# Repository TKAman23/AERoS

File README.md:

# AERoS
## An All-Encompassing Rocket System

A high-performance, compact rocket flight controller board designed around the **STM32F411RET6** microcontroller. This board integrates power management, sensor telemetry, state logging, and servo control into a single-cell Li-Po powered solution optimized for model rocketry and high-altitude aerospace tracking.

## **CRITICAL DISCLAIMER:**
*This board is currently in the active development phase. It has been fully routed and designed, but it has **NOT** been physically manufactured or bench-tested yet.*

## Board Previews & Renders

*(No 3D-models for L1, L2, and L3 were available)*

| Front 3D Render | Back 3D Render |
| :---: | :---: |
| <!-- Replace with your front render path e.g.,  -->  | <!-- Replace with your back render path e.g.,  -->  |

---

## 🛠Hardware & Board Specifications

### Core Processing & Power System
* **Microcontroller:** STM32F411RET6 (ARM Cortex-M4, 100MHz, 512KB Flash, 128KB SRAM).
* **Power Source:** Designed explicitly for a **Single-Cell Lithium-Polymer (Li-Po)** battery (~3.7V–4.2V).
* **USB Interface:** USB-C 2.0 interface supporting both data communication and **on-board USB battery charging**.
* **Power Switch:** Featuring a **self-latching MOSFET-based power switch** to enable digital soft-on/soft-off control or mechanical/pyrotechnic separation deployment triggers.
* **Actuator Power:** Integrated **Step-up (Boost) Converter** dedicated to delivering stable, elevated voltages required for servo actuation.

### Peripherals & User Interface
* **Indicators:** 3x Addressable/Configurable **RGB LEDs** for real-time state indication (e.g., pre-flight, armed, error, data logging active).
* **Acoustic Telemetry:** On-board **Piezo Buzzer** for audible flight readiness chirps, continuity checks, and recovery beacons.
* **Storage:** **D3AT SD Card Slot** wired via high-speed interface for high-rate blackbox flight logging.
* **Debugging:** Dedicated **ST-Link Connector** for SWD programming, flashing, and real-time debugging.

---

### System Architecture
<!-- Space for top-level or sheet-specific schematic screenshots as they relate to system blocks -->
```
   +-----------------------------------------------------------------+
   |                        USB-C 2.0 / Charger                      |
   +-----------------------------------------------------------------+
        |                           |
        v                           v
   +-------+           +-------------------------+           +-------+
   | Battery| ------>  | Self-Latching MOSFET SW |  -------> | Regs  |
   +-------+           +-------------------------+           +-------+
                                                                 |
            +-----------------------+------------+---------------|
            |                                    |               v
            v                                    v       +---------------+
   +-----------------+                  +------------+   | Servo Boost   |
   | STM32F411RET6   | <--- SPI/I2C --- | Sensor Bus |   +---------------+
   | Microcontroller |                  +------------+           |
   +-----------------+------+                                    v
    |      |        |       | ---------------------------> [ Servo Pins ]
    v      v        v       v
  [LEDs][Buzzer][SD Card][ST-Link]
```
For schematics, open the project file through KiCad 9.0 (can be found in the `board` directory)

<!-- #### Schematic Insights -->
<!-- <!-- Replace the placeholders below with cropped screenshots of your multi-sheet KiCad schematics -->
<!-- * **Power Management Sheet:** * *Includes USB charging circuit, battery protection, self-latching MOSFET stage, and the servo boost regulator.* -->
<!--     * <!--  --> **[Insert Power & Latching Schematic Screenshot Here]** -->
<!-- * **MCU & Breakouts Sheet:** -->
<!--     * *Includes STM32 pinouts, crystal oscillators, decoupling capacitors, and ST-Link header.* -->
<!--     * <!--  --> **[Insert MCU Core Schematic Screenshot Here]** -->

---

## On-Board Sensors

The sensor suite communicates over optimized I2C/SPI buses to provide highly accurate 9-DOF inertial, environmental, and barometric data.

| Sensor Part Number | Type | Primary Flight Function |
| :--- | :--- | :--- |
| **BMI270** | 6-Axis IMU (Accel/Gyro) | Rocket orientation, acceleration profiling, launch detection, and apogee sensing. |
| **BMP390L** | High-Precision Barometer | Precise altitude tracking, descent-rate monitoring, and main/drogue parachute deployment triggering. |
| **SHTC3** | Humidity & Temp Sensor | Environmental monitoring and internal enclosure/payload bay diagnostics. |

---

## Design & Development

* **EDA Software:** Designed completely using **KiCad**.
* **Firmware Compatibility:** Perfect pairing with STM32CubeIDE, HAL libraries, or custom bare-metal C/C++ architectures.

### Future Scope / Additions (To-Do)
- [ ] Physical PCB manufacturing and assembly (PCBA evaluation).
- [ ] Continuity testing on the self-latching MOSFET network.
- [ ] Bench testing the Step-Up regulator under maximum servo load.
- [ ] Developing a comprehensive flight firmware stack (Blackbox logging framework, Kalman filtering for apogee detection).
- [ ] Pinout map cheat-sheet (Markdown table matching STM32 pins to hardware blocks).

---

## License & Copyright

This project is licensed under the **GNU GPL v3** License. 

```
Copyright (c) 2026 Karthikeya Turimalla (TKAman23)

This program is free software: you can redistribute it and/or modify
it under the terms of the GNU General Public License as published by
the Free Software Foundation, either version 3 of the License, or
(at your option) any later version.
```
See the accompanying `LICENSE` file for full terms and conditions.

---

## Attribution Request

If you use parts of this repository, please reference the repository, my username (TKAman23), or me (Karthikeya Turimalla) in your work.

---

## Contributing & Feedback

Since this project is in active prototyping, discussions, issues, and pull requests regarding optimization (especially around power management and thermal layout) are generally welcome!
Contact: [karthikeyaat@gmail.com](mailto:karthikeyaat@gmail.com).

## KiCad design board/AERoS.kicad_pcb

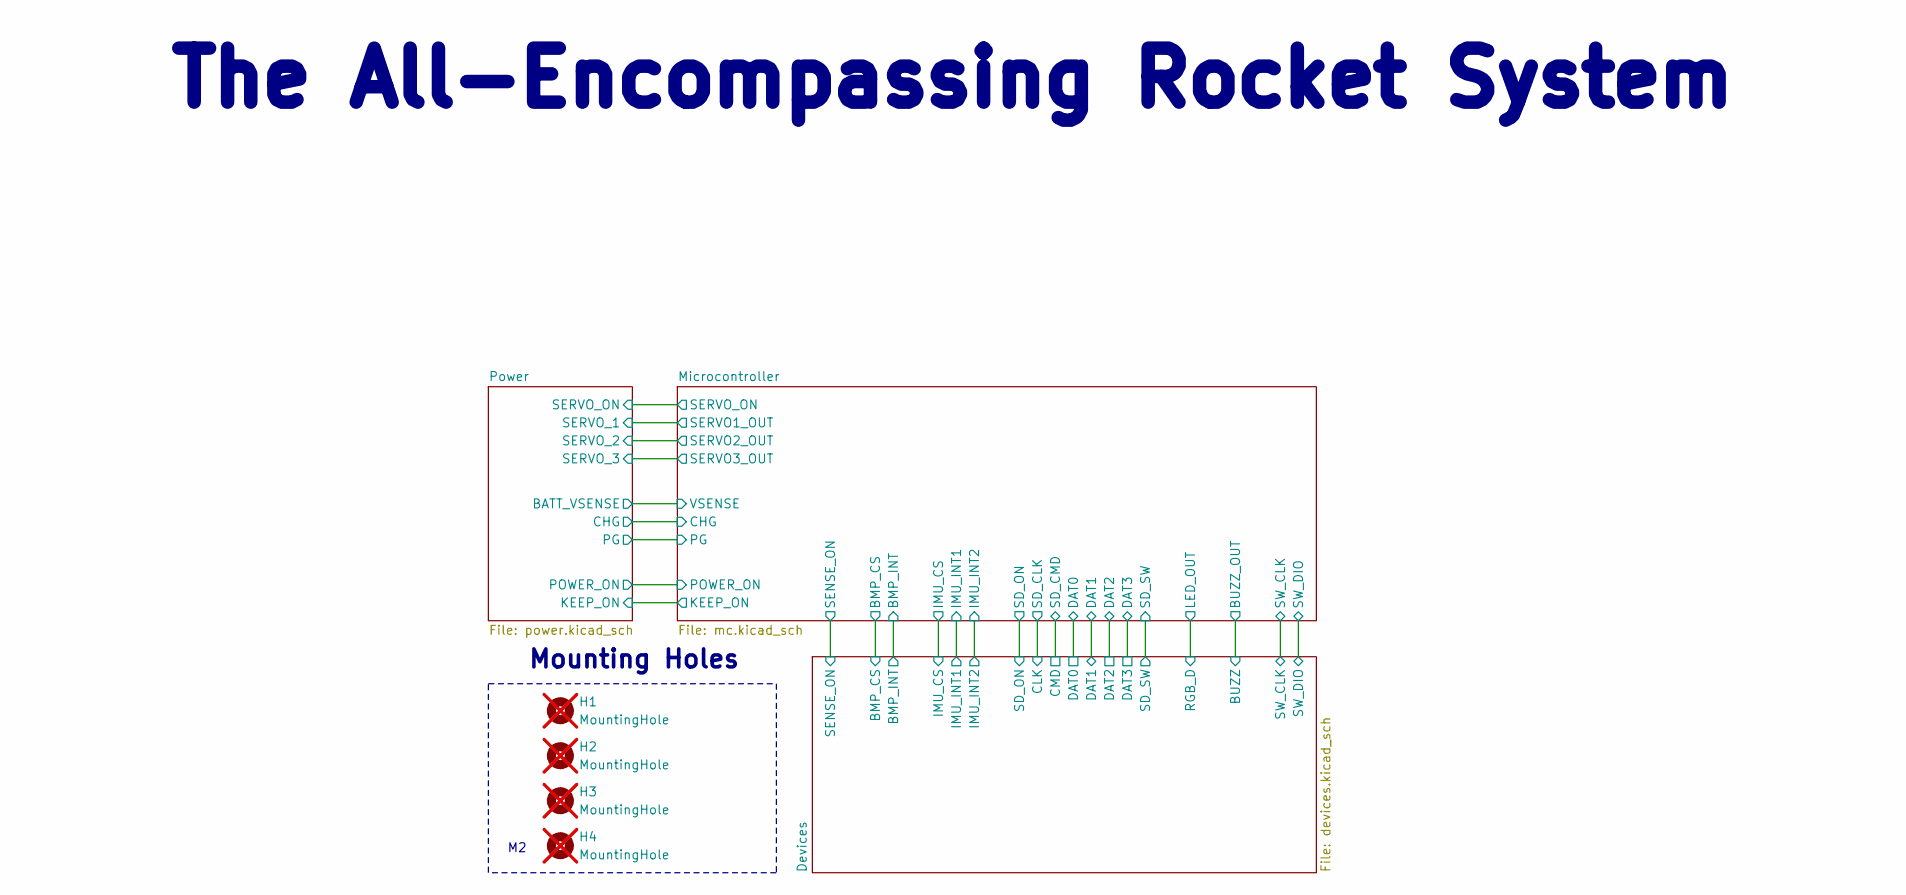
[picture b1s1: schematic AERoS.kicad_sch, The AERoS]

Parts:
H1, H2, H3, H4: MountingHole; MountingHole_2.2mm_M2; not fitted

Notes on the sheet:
Mounting Holes
The All-Encompassing Rocket System

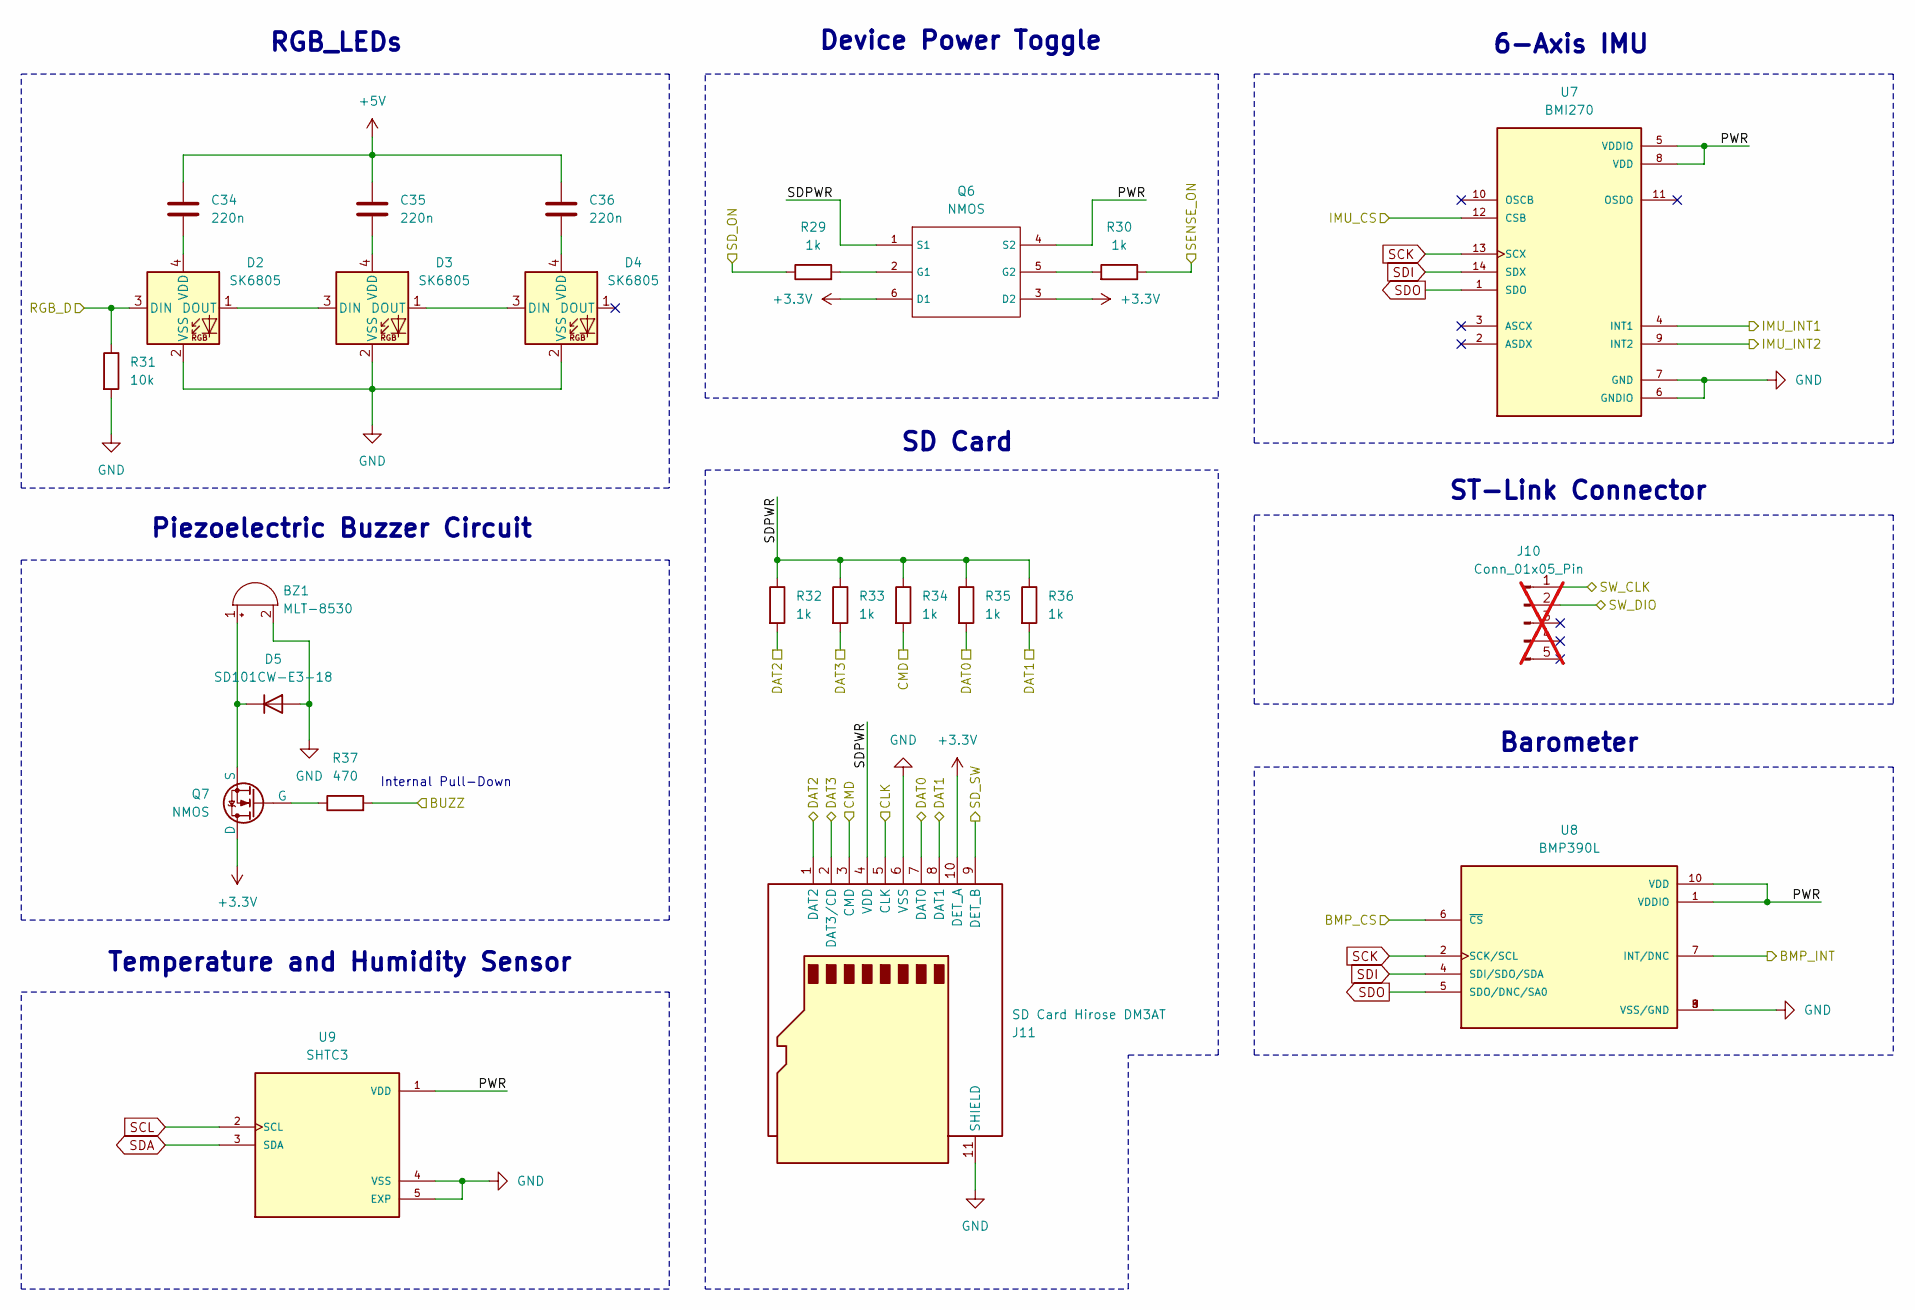
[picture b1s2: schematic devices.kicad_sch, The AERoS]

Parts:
BZ1: MLT-8530; MLT-8530_JHE; MFR. Part # MLT-8530; JLCPCB Part # C94599
C34, C35, C36: 220n; C_0402_1005Metric; MFR. Part # CL05B224KO5NNNC; JLCPCB Part # C16772
D2, D3, D4: SK6805; SK6805-EC15; MFR. Part # SK6805-EC15; JLCPCB Part # C2890035
D5: SD101CW-E3-18; D_SOD-123; MFR. Part # SD101CW-E3-18; JLCPCB Part # C3313033
J10: Conn_01x05_Pin; PinHeader_1x05_P2.54mm_Vertical; not fitted
J11: SD Card Hirose DM3AT; microSD_HC_Hirose_DM3AT-SF-PEJM5; MFR. Part # DM3AT-SF-PEJM5; JLCPCB Part # C114218
Q6: NMOS; SOT-363_SC-70-6; MFR. Part # NTJD5121NT1G; JLCPCB Part # C15215
Q7: NMOS; DFN-3(0.6x1); MFR. Part # YJA3134KB; JLCPCB Part # C20605534
R29, R30, R32, R33, R34, R35, R36: 1k; R_0402_1005Metric; MFR. Part # 0402WGF1001TCE; JLCPCB Part # C11702
R31: 10k; R_0402_1005Metric; MFR. Part # 0402WGF1002TCE; JLCPCB Part # C25744
R37: 470; R_0402_1005Metric; MFR. Part # 0402WGF4700TCE; JLCPCB Part # C25117
U7: BMI270; XDCR_BMI270; MFR. Part # BMI270; JLCPCB Part # C2836813
U8: BMP390L; XDCR_BMP390L; PARTREV 1.7; JLCPCB Part # C2684802
U9: SHTC3; SON100P200X200X80-5N; PARTREV 3; JLCPCB Part # C194656

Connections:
+3.3V: J11.10 (DET_A), Q6.3 (D2), Q6.6 (D1), Q7.1 (D); also elsewhere on the board
+5V: C34.1, C35.1, C36.1; also elsewhere on the board
/Devices/BMP_CS: U8.6 (~CS); also elsewhere on the board
/Devices/BMP_INT: U8.7 (INT/DNC); also elsewhere on the board
/Devices/BUZZ: R37.2; also elsewhere on the board
/Devices/CLK: J11.5 (CLK); also elsewhere on the board
/Devices/CMD: J11.3 (CMD), R34.2; also elsewhere on the board
/Devices/DAT0: J11.7 (DAT0), R35.2; also elsewhere on the board
/Devices/DAT1: J11.8 (DAT1), R36.2; also elsewhere on the board
/Devices/DAT2: J11.1 (DAT2), R32.2; also elsewhere on the board
/Devices/DAT3: J11.2 (DAT3/CD), R33.2; also elsewhere on the board
/Devices/IMU_CS: U7.12 (CSB); also elsewhere on the board
/Devices/IMU_INT1: U7.4 (INT1); also elsewhere on the board
/Devices/IMU_INT2: U7.9 (INT2); also elsewhere on the board
/Devices/PWR: Q6.4 (S2), U7.5 (VDDIO), U7.8 (VDD), U8.1 (VDDIO), U8.10 (VDD), U9.1 (VDD)
/Devices/RGB_D: D2.3 (DIN), R31.1; also elsewhere on the board
/Devices/SDPWR: J11.4 (VDD), Q6.1 (S1), R32.1, R33.1, R34.1, R35.1, R36.1
/Devices/SD_ON: R29.1; also elsewhere on the board
/Devices/SD_SW: J11.9 (DET_B); also elsewhere on the board
/Devices/SENSE_ON: R30.1; also elsewhere on the board
/Devices/SW_CLK: J10.1; also elsewhere on the board
/Devices/SW_DIO: J10.2; also elsewhere on the board
GND: BZ1.2 (-), D2.2 (VSS), D3.2 (VSS), D4.2 (VSS), D5.2 (A), J11.6 (VSS), J11.11 (SHIELD), R31.2, U7.6 (GNDIO), U7.7 (GND), U8.3 (VSS/GND), U8.8 (VSS/GND), U8.9 (VSS/GND), U9.4 (VSS), U9.5 (EXP); also elsewhere on the board
unnamed: BZ1.1 (+), D5.1 (K), Q7.3 (S)
unnamed: D2.1 (DOUT), D3.3 (DIN)
unnamed: C34.2, D2.4 (VDD)
unnamed: D3.1 (DOUT), D4.3 (DIN)
unnamed: C35.2, D3.4 (VDD)
unnamed: C36.2, D4.4 (VDD)
unnamed: Q6.2 (G1), R29.2
unnamed: Q6.5 (G2), R30.2
unnamed: Q7.2 (G), R37.1
SCK: U7.13 (SCX), U8.2 (SCK/SCL); also elsewhere on the board
SCL: U9.2 (SCL); also elsewhere on the board
SDA: U9.3 (SDA); also elsewhere on the board
SDI: U7.14 (SDX), U8.4 (SDI/SDO/SDA); also elsewhere on the board
SDO: U7.1 (SDO), U8.5 (SDO/DNC/SA0); also elsewhere on the board

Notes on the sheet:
RGB_LEDs
6-Axis IMU
Internal Pull-Down
Device Power Toggle
Barometer
Piezoelectric Buzzer Circuit
Temperature and Humidity Sensor
SD Card
ST-Link Connector

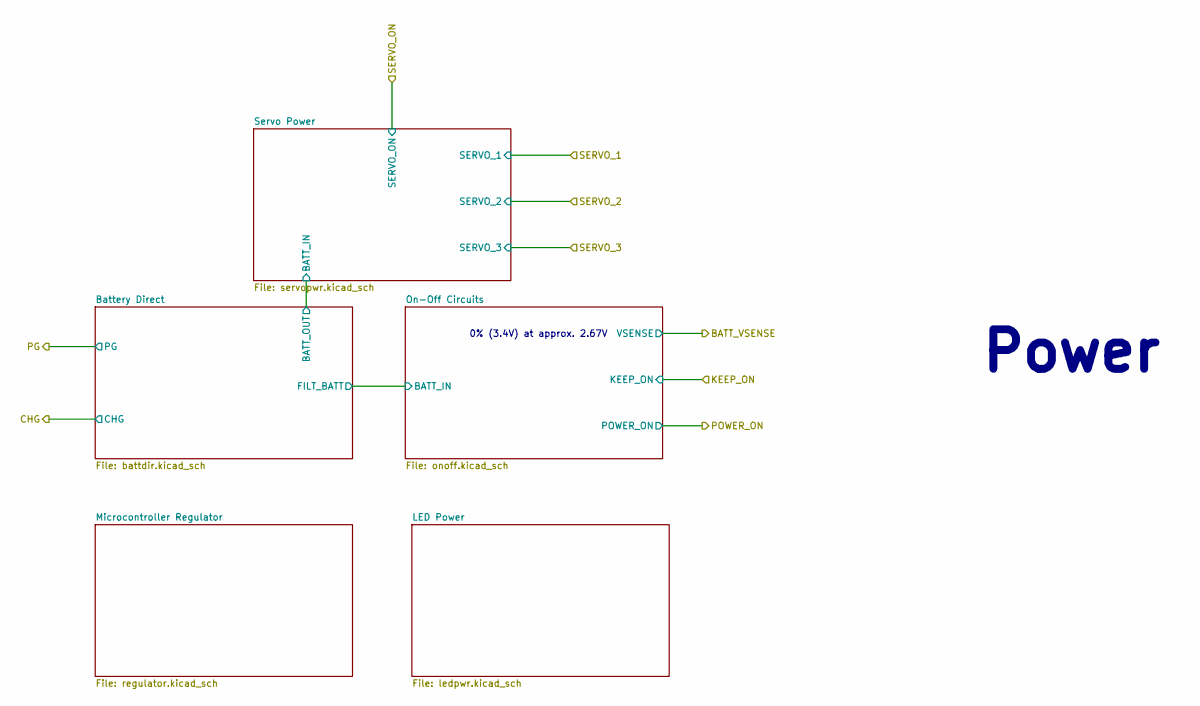
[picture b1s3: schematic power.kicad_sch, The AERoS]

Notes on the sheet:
Power
0% (3.4V) at approx. 2.67V

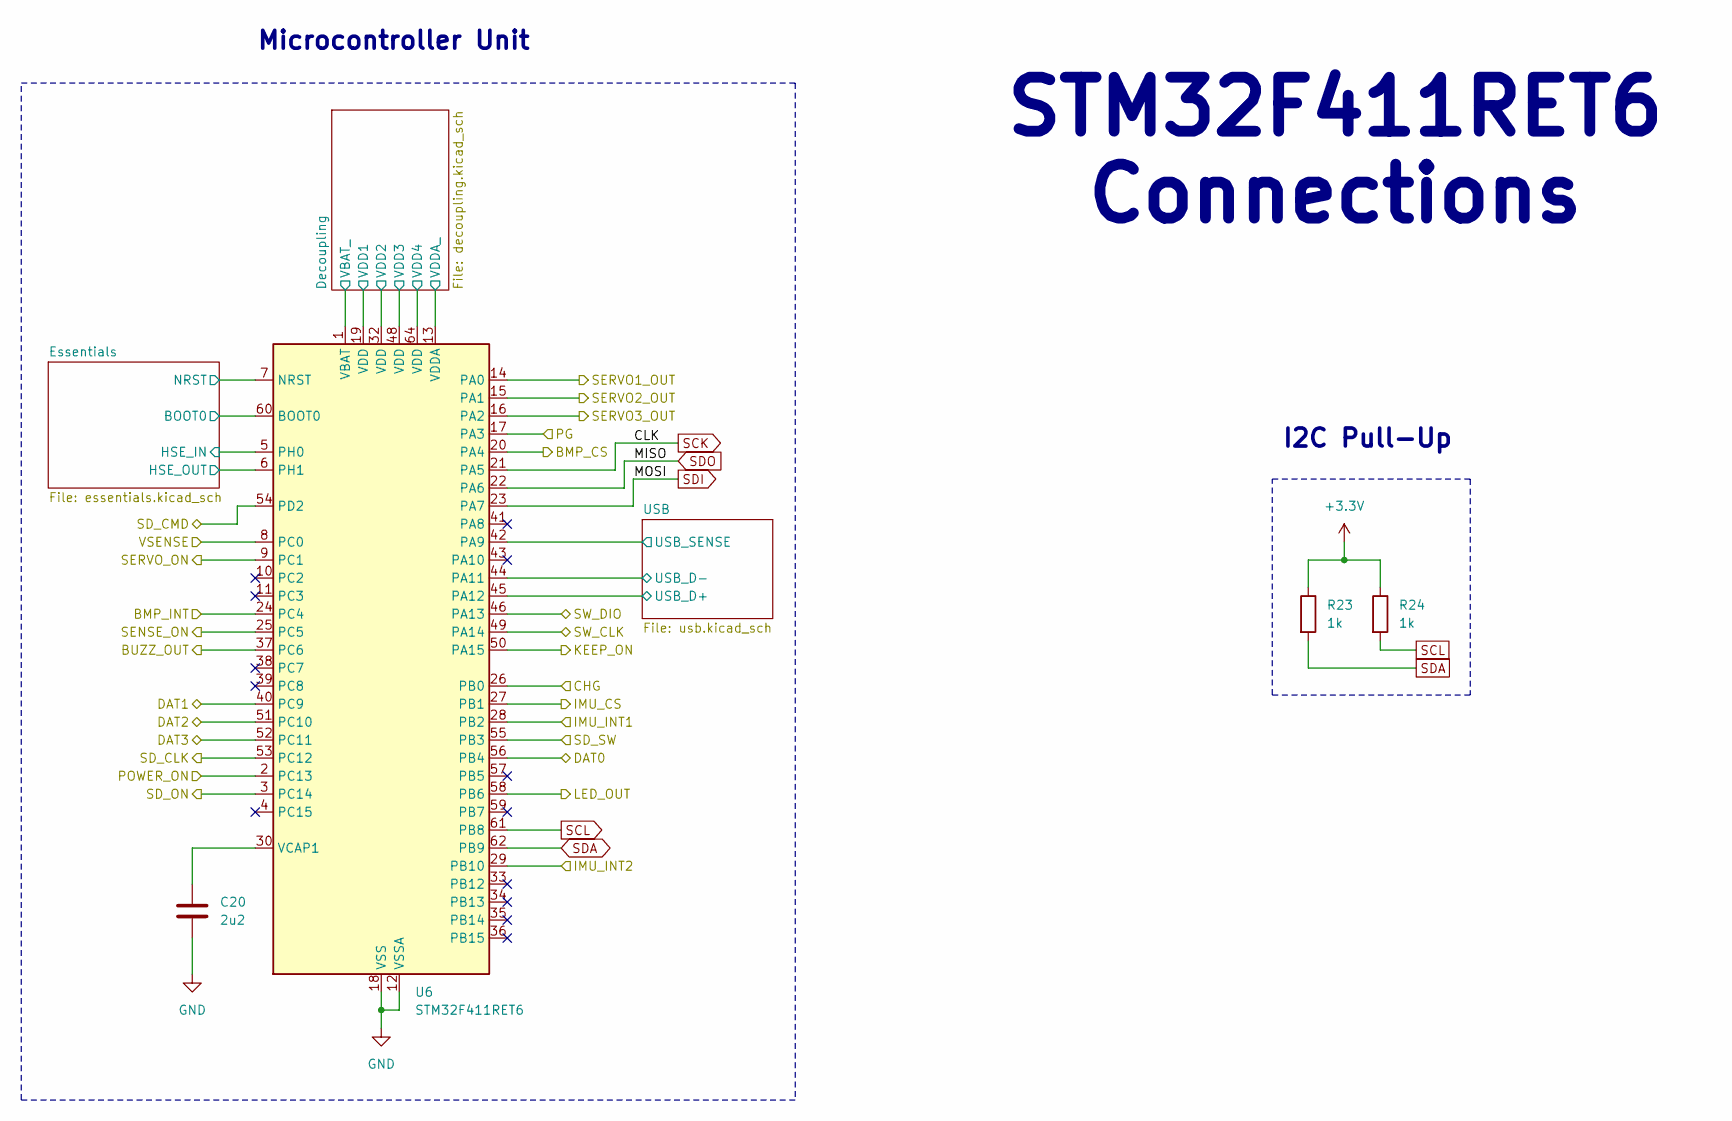
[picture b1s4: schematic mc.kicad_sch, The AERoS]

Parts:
C20: 2u2; C_0603_1608Metric; MFR. Part # CL10A225KO8NNNC; JLCPCB Part # C23630
R23, R24: 1k; R_0402_1005Metric; MFR. Part # 0402WGF1001TCE; JLCPCB Part # C11702
U6: STM32F411RET6; LQFP-64_10x10mm_P0.5mm; MFR. Part # STM32F411RET6; JLCPCB Part # C94355

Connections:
+3.3V: R23.1, R24.1, U6.1 (VBAT), U6.19 (VDD), U6.32 (VDD), U6.48 (VDD), U6.64 (VDD); also elsewhere on the board
/Devices/BMP_CS: U6.20 (PA4); also elsewhere on the board
/Devices/BMP_INT: U6.24 (PC4); also elsewhere on the board
/Devices/BUZZ: U6.37 (PC6); also elsewhere on the board
/Devices/CLK: U6.53 (PC12); also elsewhere on the board
/Devices/CMD: U6.54 (PD2); also elsewhere on the board
/Devices/DAT0: U6.56 (PB4); also elsewhere on the board
/Devices/DAT1: U6.40 (PC9); also elsewhere on the board
/Devices/DAT2: U6.51 (PC10); also elsewhere on the board
/Devices/DAT3: U6.52 (PC11); also elsewhere on the board
/Devices/IMU_CS: U6.27 (PB1); also elsewhere on the board
/Devices/IMU_INT1: U6.28 (PB2); also elsewhere on the board
/Devices/IMU_INT2: U6.29 (PB10); also elsewhere on the board
/Devices/RGB_D: U6.58 (PB6); also elsewhere on the board
/Devices/SD_ON: U6.3 (PC14); also elsewhere on the board
/Devices/SD_SW: U6.55 (PB3); also elsewhere on the board
/Devices/SENSE_ON: U6.25 (PC5); also elsewhere on the board
/Devices/SW_CLK: U6.49 (PA14); also elsewhere on the board
/Devices/SW_DIO: U6.46 (PA13); also elsewhere on the board
/Microcontroller/CHG: U6.26 (PB0); also elsewhere on the board
/Microcontroller/Decoupling/VDDA_: U6.13 (VDDA); also elsewhere on the board
/Microcontroller/Essentials/BOOT0: U6.60 (BOOT0); also elsewhere on the board
/Microcontroller/Essentials/HSE_IN: U6.5 (PH0); also elsewhere on the board
/Microcontroller/Essentials/HSE_OUT: U6.6 (PH1); also elsewhere on the board
/Microcontroller/Essentials/NRST: U6.7 (NRST); also elsewhere on the board
/Microcontroller/KEEP_ON: U6.50 (PA15); also elsewhere on the board
/Microcontroller/PG: U6.17 (PA3); also elsewhere on the board
/Microcontroller/POWER_ON: U6.2 (PC13); also elsewhere on the board
/Microcontroller/SERVO1_OUT: U6.14 (PA0); also elsewhere on the board
/Microcontroller/SERVO2_OUT: U6.15 (PA1); also elsewhere on the board
/Microcontroller/SERVO3_OUT: U6.16 (PA2); also elsewhere on the board
/Microcontroller/SERVO_ON: U6.9 (PC1); also elsewhere on the board
/Microcontroller/USB/USB_D+: U6.45 (PA12); also elsewhere on the board
/Microcontroller/USB/USB_D-: U6.44 (PA11); also elsewhere on the board
/Microcontroller/USB/USB_SENSE: U6.42 (PA9); also elsewhere on the board
/Microcontroller/VSENSE: U6.8 (PC0); also elsewhere on the board
GND: C20.2, U6.12 (VSSA), U6.18 (VSS), U6.31 (VSS), U6.47 (VSS), U6.63 (VSS); also elsewhere on the board
unnamed: C20.1, U6.30 (VCAP1)
SCK: U6.21 (PA5); also elsewhere on the board
SCL: R24.2, U6.61 (PB8); also elsewhere on the board
SDA: R23.2, U6.62 (PB9); also elsewhere on the board
SDI: U6.23 (PA7); also elsewhere on the board
SDO: U6.22 (PA6); also elsewhere on the board

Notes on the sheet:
I2C Pull-Up
Microcontroller Unit
STM32F411RET6 Connections

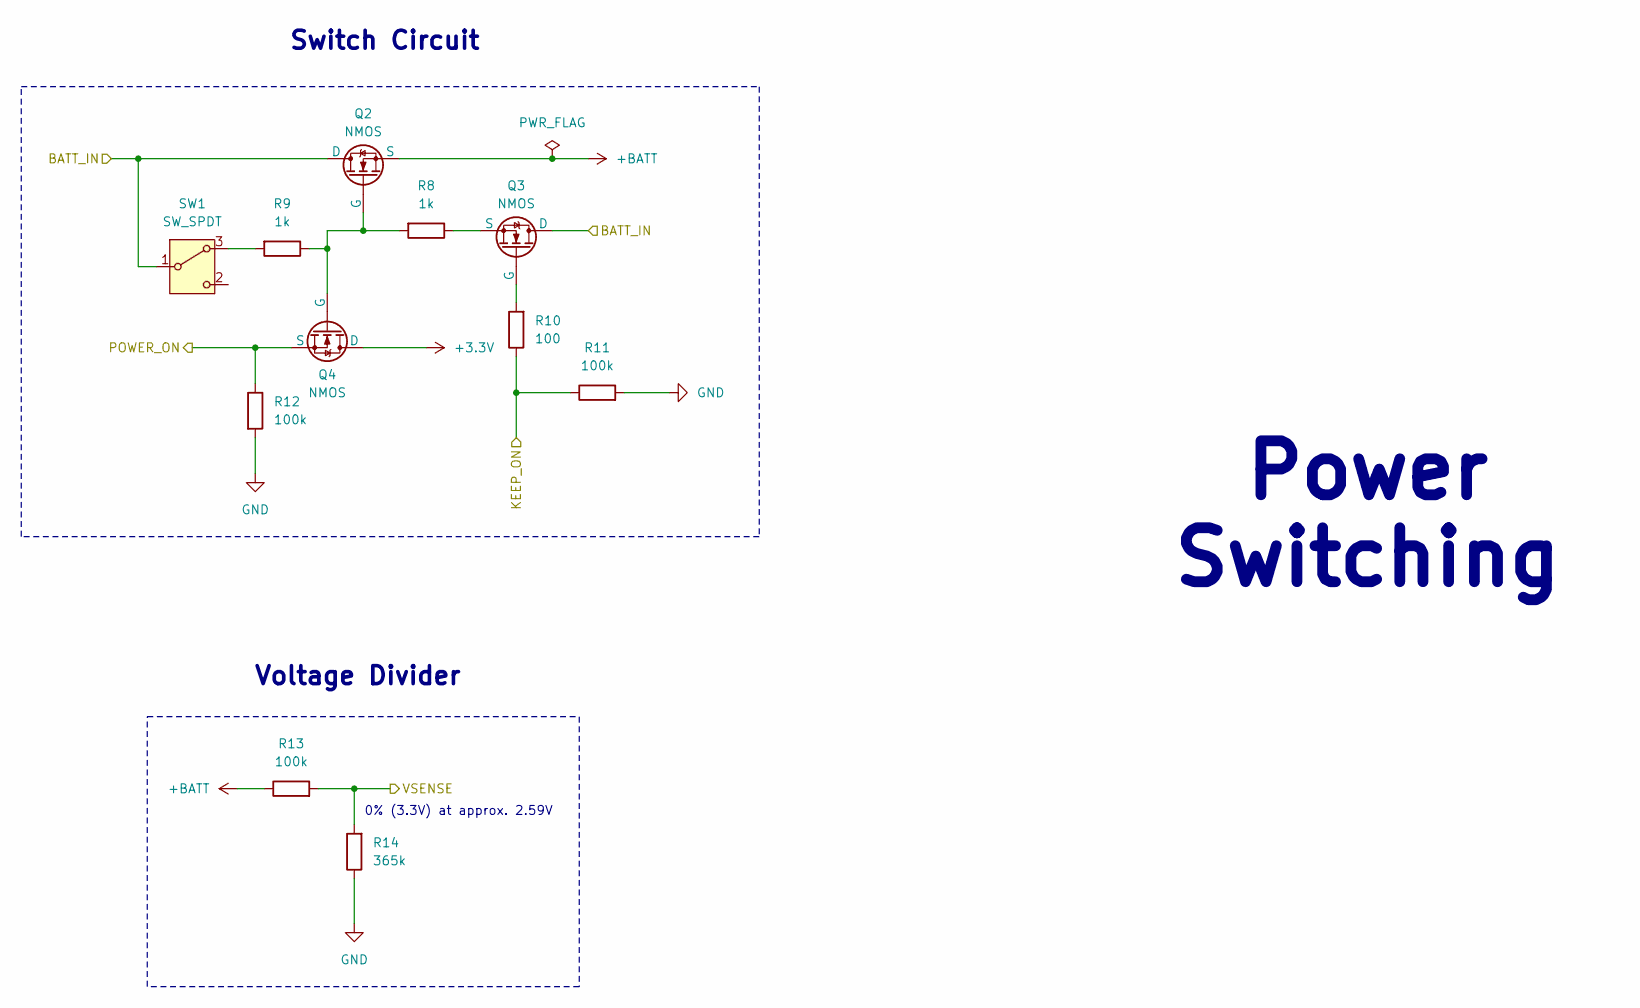
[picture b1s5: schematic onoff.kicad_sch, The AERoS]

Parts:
Q2, Q3, Q4: NMOS; DFN-3(0.6x1); MFR. Part # YJA3134KB; JLCPCB Part # C20605534
R8, R9: 1k; R_0402_1005Metric; MFR. Part # 0402WGF1001TCE; JLCPCB Part # C11702
R10: 100; R_0402_1005Metric; MFR. Part # 0402WGF1000TCE; JLCPCB Part # C25076
R11, R12, R13: 100k; R_0402_1005Metric; MFR. Part # 0402WGF1003TCE; JLCPCB Part # C25741
R14: 365k; R_0402_1005Metric; MFR. Part # 0402WGF3653TCE; JLCPCB Part # C27006
SW1: SW_SPDT; MK-12C02-G020_GSW; MFR. Part # MK-12C02-G020_GSW; JLCPCB Part # C963206

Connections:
+3.3V: Q4.1 (D); also elsewhere on the board
+BATT: Q2.3 (S), R13.1; also elsewhere on the board
/Microcontroller/KEEP_ON: R10.1, R11.1; also elsewhere on the board
/Microcontroller/POWER_ON: Q4.3 (S), R12.1; also elsewhere on the board
/Microcontroller/VSENSE: R13.2, R14.2; also elsewhere on the board
/Power/Battery Direct/FILT_BATT: Q2.1 (D), Q3.1 (D), SW1.1 (B); also elsewhere on the board
GND: R11.2, R12.2, R14.1; also elsewhere on the board
unnamed: Q2.2 (G), Q4.2 (G), R8.2, R9.1
unnamed: Q3.2 (G), R10.2
unnamed: Q3.3 (S), R8.1
unnamed: R9.2, SW1.3 (A)

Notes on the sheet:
Power Switching
0% (3.3V) at approx. 2.59V
Switch Circuit
Voltage Divider

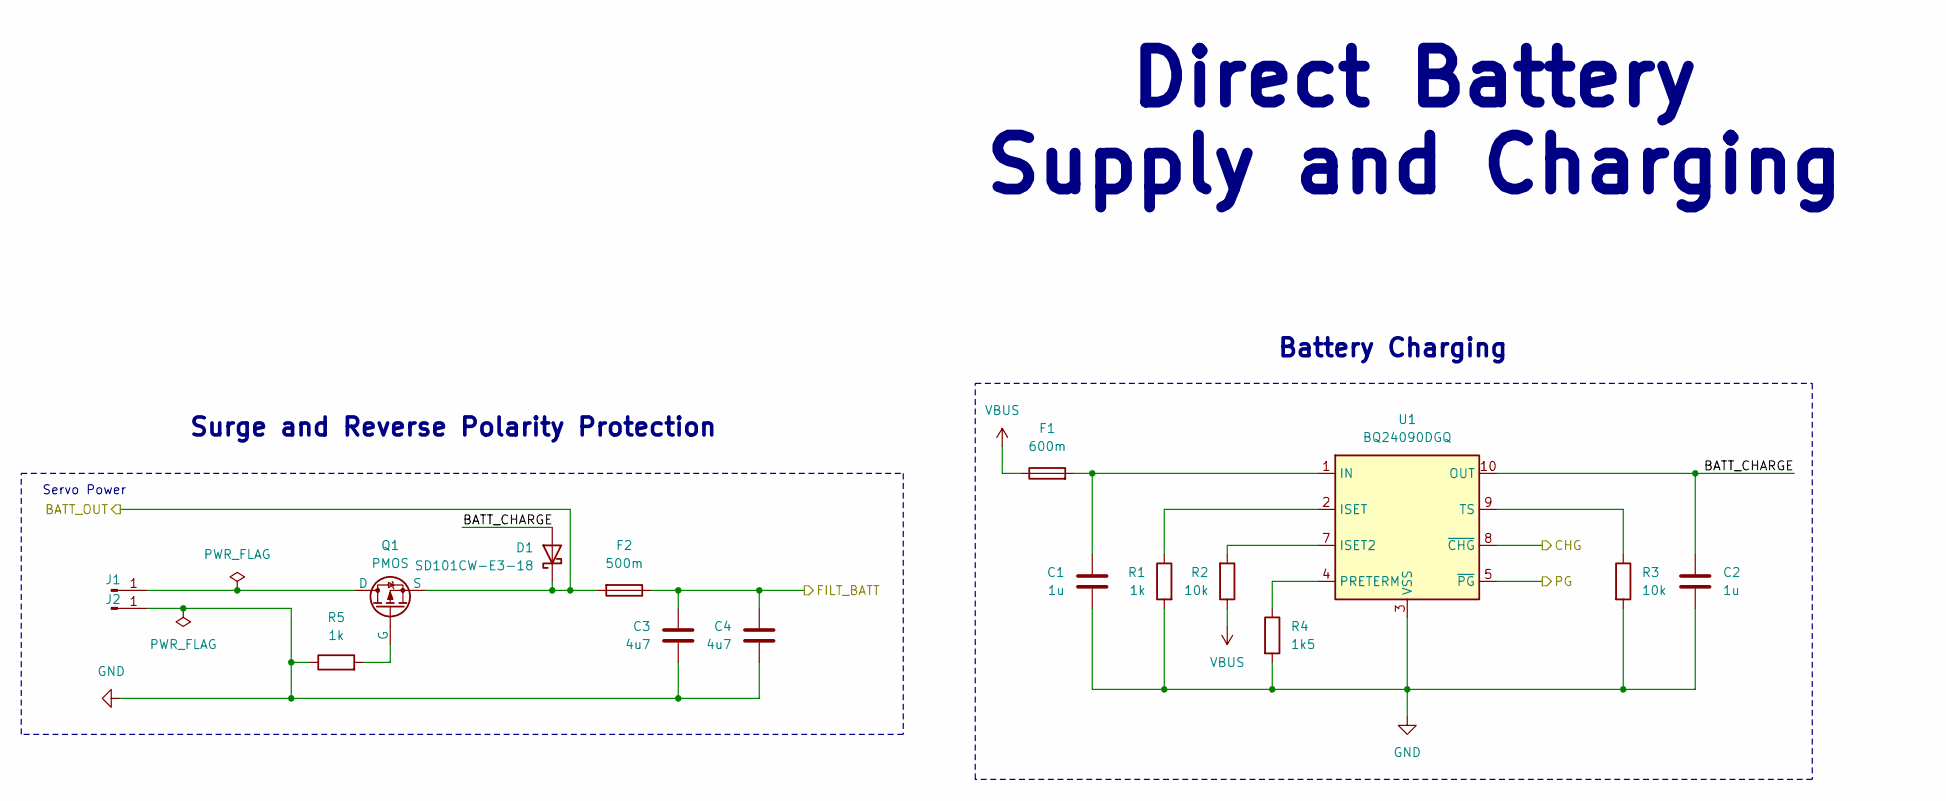
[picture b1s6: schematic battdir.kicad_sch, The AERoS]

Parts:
C1, C2: 1u; C_0402_1005Metric; MFR. Part # CL05A105KP5NNNC; JLCPCB Part # C14445
C3, C4: 4u7; C_0805_2012Metric; MFR. Part # CL21A475KAQNNNE; JLCPCB Part # C1779
D1: SD101CW-E3-18; D_SOD-123; MFR. Part # SD101CW-E3-18; JLCPCB Part # C3313033
F1: 600m; Fuse_1206_3216Metric; MFR. Part # 1206L050/24WR; JLCPCB Part # C2154056
F2: 500m; Fuse_1206_3216Metric; MFR. Part # SMD1206P025TF; JLCPCB Part # C20798
J1, J2: Conn_01x01_Pin; Pad_4x4mm
Q1: PMOS; DFN-6-2EP_(AGM20P16AS); MFR. Part # AGM20P16AS; JLCPCB Part # C18221388
R1, R5: 1k; R_0402_1005Metric; MFR. Part # 0402WGF1001TCE; JLCPCB Part # C11702
R2, R3: 10k; R_0402_1005Metric; MFR. Part # 0402WGF1002TCE; JLCPCB Part # C25744
R4: 1k5; R_0402_1005Metric; MFR. Part # 0402WGF1501TCE; JLCPCB Part # C25867
U1: BQ24090DGQ; HVSSOP-10-1EP_3x3mm_P0.5mm_EP1.57x1.88mm_ThermalVias; MFR. Part # BQ24090DGQR; JLCPCB Part # C43306

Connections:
/Microcontroller/CHG: U1.8 (~CHG); also elsewhere on the board
/Microcontroller/PG: U1.5 (~PG); also elsewhere on the board
/Power/Battery Direct/BATT_CHARGE: C2.1, D1.2 (A), U1.10 (OUT)
/Power/Battery Direct/BATT_OUT: D1.1 (K), F2.2, Q1.3 (S); also elsewhere on the board
/Power/Battery Direct/FILT_BATT: C3.2, C4.2, F2.1; also elsewhere on the board
GND: C1.2, C2.2, C3.1, C4.1, J2.1, R1.2, R3.2, R4.2, R5.1, U1.3 (VSS), U1.11 (VSS); also elsewhere on the board
unnamed: J1.1, Q1.1 (D)
unnamed: Q1.2 (G), R5.2
unnamed: C1.1, F1.2, U1.1 (IN)
unnamed: R2.2, U1.7 (ISET2)
unnamed: R1.1, U1.2 (ISET)
unnamed: R4.1, U1.4 (PRETERM)
unnamed: R3.1, U1.9 (TS)
VBUS: F1.1, R2.1; also elsewhere on the board

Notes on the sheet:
Battery Charging
Surge and Reverse Polarity Protection
Direct Battery Supply and Charging
Servo Power

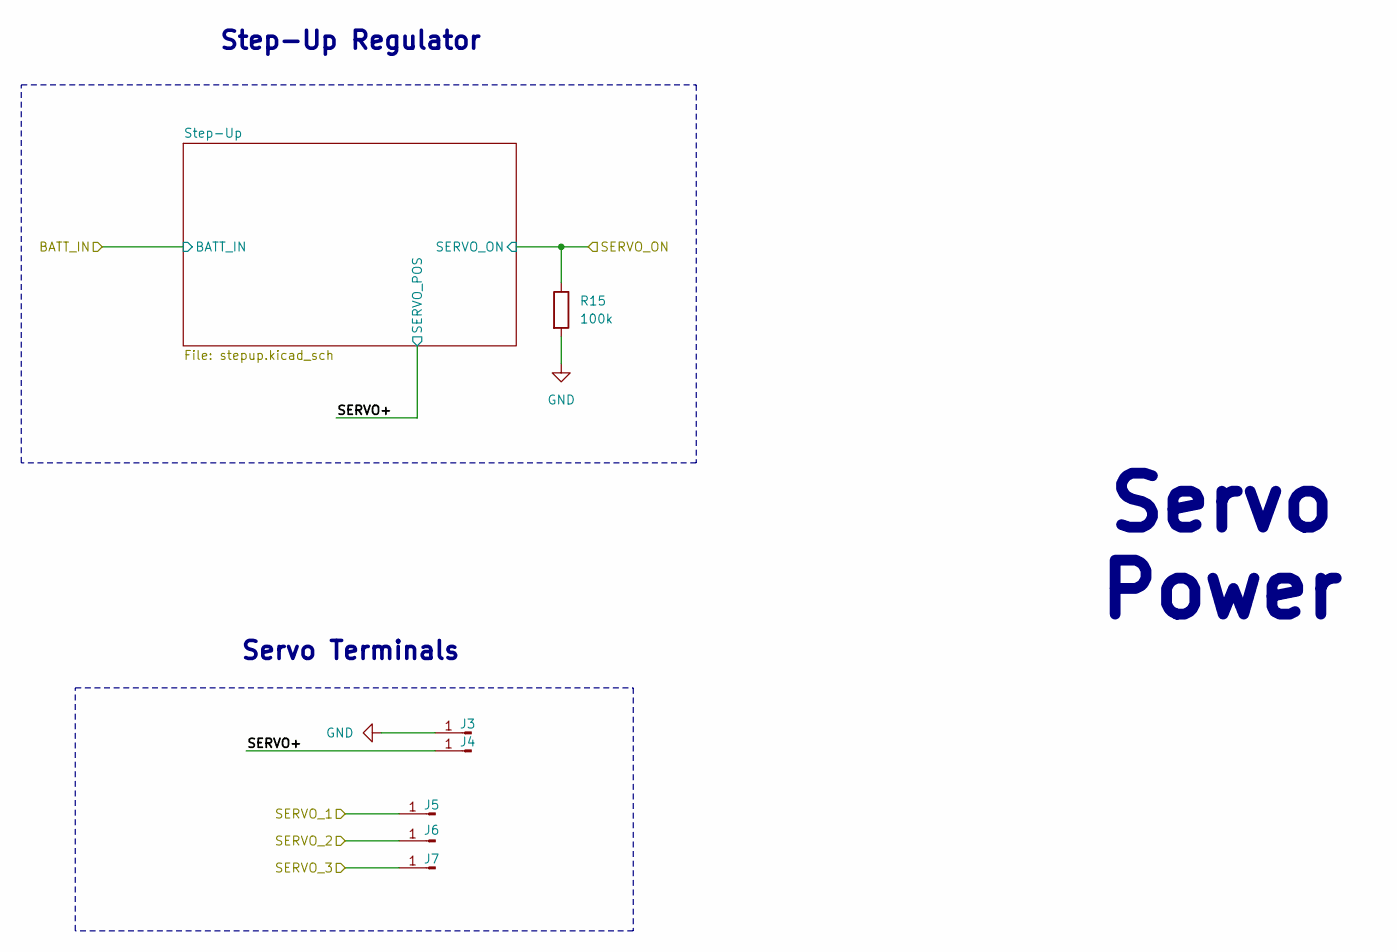
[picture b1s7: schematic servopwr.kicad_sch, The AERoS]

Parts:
J3, J4: Conn_01x01_Pin; Pad_3x3mm
J5, J6, J7: Conn_01x01_Pin; SolderWirePad_1x01_SMD_1x2mm
R15: 100k; R_0402_1005Metric; MFR. Part # 0402WGF1003TCE; JLCPCB Part # C25741

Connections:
/Microcontroller/SERVO1_OUT: J5.1; also elsewhere on the board
/Microcontroller/SERVO2_OUT: J6.1; also elsewhere on the board
/Microcontroller/SERVO3_OUT: J7.1; also elsewhere on the board
/Microcontroller/SERVO_ON: R15.1; also elsewhere on the board
/Power/Servo Power/SERVO+: J4.1; also elsewhere on the board
GND: J3.1, R15.2; also elsewhere on the board

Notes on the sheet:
Step-Up Regulator
Servo Power
Servo Terminals

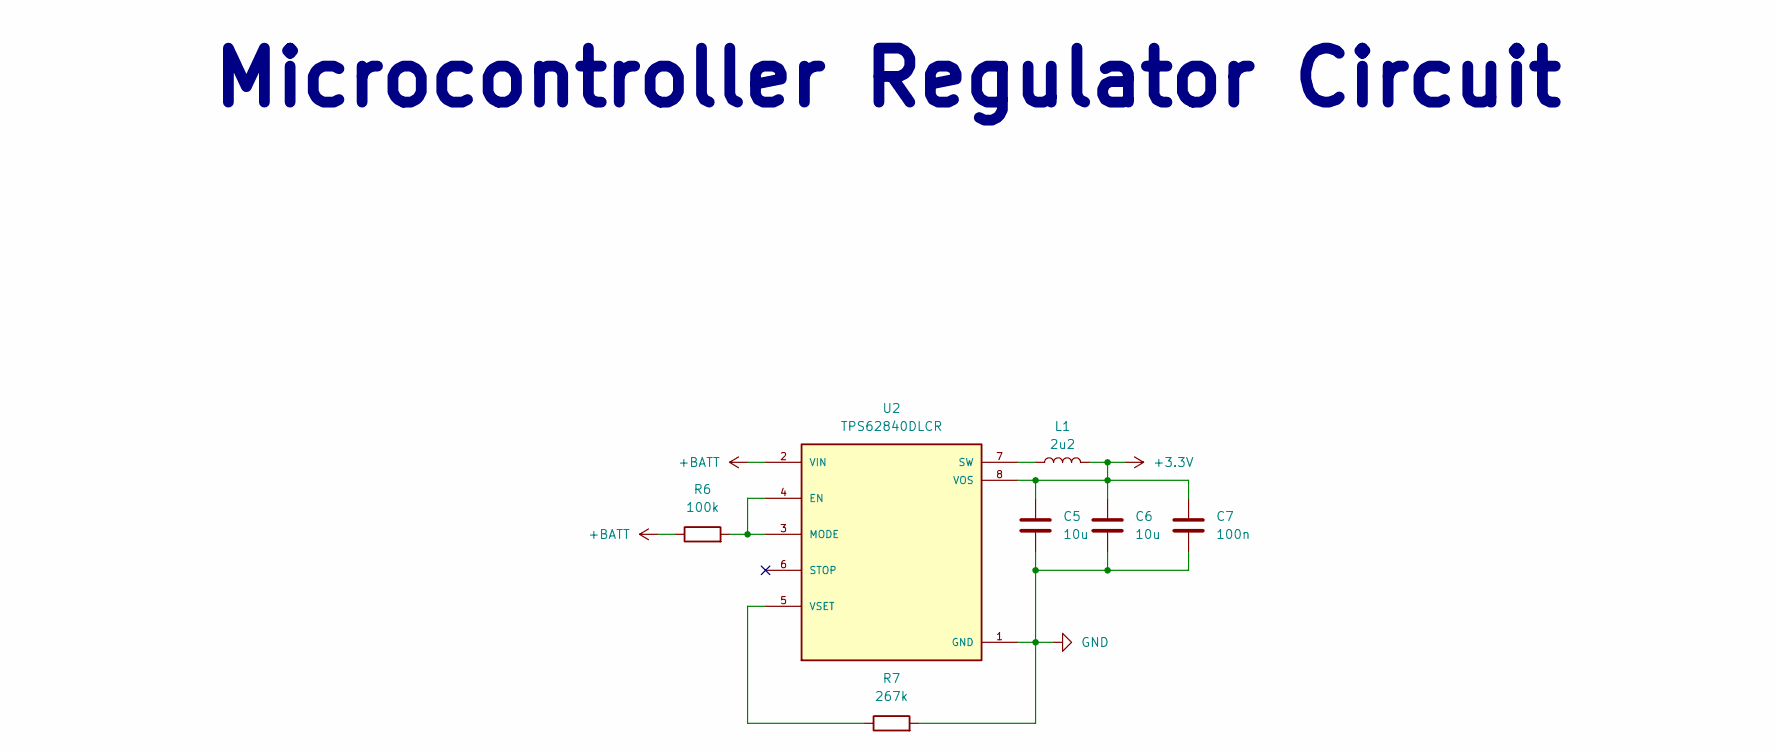
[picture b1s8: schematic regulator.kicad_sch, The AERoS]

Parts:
C5, C6: 10u; C_0805_2012Metric; MFR. Part # CL21A106KAYNNNE; JLCPCB Part # C15850
C7: 100n; C_0402_1005Metric; MFR. Part # CL05B104KO5NNNC; JLCPCB Part # C1525
L1: 2u2; IND_LQH2MPZ2R2MGRL; MFR. Part # LQH2MPZ2R2MGRL; JLCPCB Part # C2042050
R6: 100k; R_0402_1005Metric; MFR. Part # 0402WGF1003TCE; JLCPCB Part # C25741
R7: 267k; R_0402_1005Metric; MFR. Part # 0402WGF2673TCE; JLCPCB Part # C270622
U2: TPS62840DLCR; SON50P200X150X100-8N; MFR. Part # TPS62840DLCR; JLCPCB Part # C2071859

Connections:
+3.3V: C5.2, C6.2, C7.2, L1.2, U2.8 (VOS); also elsewhere on the board
+BATT: R6.1, U2.2 (VIN); also elsewhere on the board
GND: C5.1, C6.1, C7.1, R7.2, U2.1 (GND); also elsewhere on the board
unnamed: R6.2, U2.3 (MODE), U2.4 (EN)
unnamed: L1.1, U2.7 (SW)
unnamed: R7.1, U2.5 (VSET)

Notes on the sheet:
Microcontroller Regulator Circuit

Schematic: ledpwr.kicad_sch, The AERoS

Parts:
C18: 4u7; C_0805_2012Metric; MFR. Part # CL21A475KAQNNNE; JLCPCB Part # C1779
C19: 10u; C_0805_2012Metric; MFR. Part # CL21A106KAYNNNE; JLCPCB Part # C15850
L3: 2u2; IND_LQH2MPZ2R2MGRL; MFR. Part # LQH2MPZ2R2MGRL; JLCPCB Part # C2042050
R21: 976k; R_0402_1005Metric; MFR. Part # 0402WGF9763TCE; JLCPCB Part # C25802
R22: 562k; R_0402_1005Metric; MFR. Part # 0402WGF5623TCE; JLCPCB Part # C48838
U5: MCP1640x-xMC; DFN-8-1EP_3x2mm_P0.5mm_EP1.75x1.45mm; MFR. Part # MCP1640CT-I/MC; JLCPCB Part # C623037

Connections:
+5V: C19.1, R21.1, U5.6 (V_{OUT}), U5.7 (V_{OUT}); also elsewhere on the board
+BATT: C18.1, L3.1, U5.4 (EN), U5.8 (V_{IN}); also elsewhere on the board
GND: C18.2, C19.2, R22.2, U5.2 (GND), U5.3 (GND), U5.9 (GND); also elsewhere on the board
unnamed: L3.2, U5.5 (SW)
unnamed: R21.2, R22.1, U5.1 (V_{FB})

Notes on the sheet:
LED Power Regulator
LED Regulator

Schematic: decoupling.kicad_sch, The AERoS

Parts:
C21: 10u; C_0805_2012Metric; MFR. Part # CL21A106KAYNNNE; JLCPCB Part # C15850
C22, C23, C24, C25: 100n; C_0402_1005Metric; MFR. Part # CL05B104KO5NNNC; JLCPCB Part # C1525
C26: 10n; C_0402_1005Metric; MFR. Part # 0402B103K500NT; JLCPCB Part # C1524
C27, C28: 1u; C_0402_1005Metric; MFR. Part # CL05A105KP5NNNC; JLCPCB Part # C14445
FB1: GZ1608D121TF; L_0603_1608Metric; MFR. Part # GZ1608D121TF; JLCPCB Part # C12391

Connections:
+3.3V: C21.1, C22.1, C23.1, C24.1, C25.1, C28.1, FB1.2; also elsewhere on the board
/Microcontroller/Decoupling/VDDA_: C26.1, C27.1, FB1.1; also elsewhere on the board
GND: C21.2, C22.2, C23.2, C24.2, C25.2, C26.2, C27.2, C28.2; also elsewhere on the board

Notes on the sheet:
Analog
Decoupling Capacitors for STM32
Standard

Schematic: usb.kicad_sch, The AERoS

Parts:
C32: 10u; C_0603_1608Metric; MFR. Part # CL10A106MQ8NNNC; JLCPCB Part # C1691
C33: 4u7; C_0603_1608Metric; MFR. Part # CL10A475KP8NNNC; JLCPCB Part # C1705
J9: USB_C_Receptacle_USB2.0_14P; USB_C_Receptacle_G-Switch_GT-USB-7010ASV; MFR. Part # GT-USB-7010ASV; JLCPCB Part # C2988369
R26: 100k; R_0402_1005Metric; MFR. Part # 0402WGF1003TCE; JLCPCB Part # C25741
R27, R28: 5k1; R_0402_1005Metric; MFR. Part # 0402WGF5101TCE; JLCPCB Part # C25905

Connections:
/Microcontroller/USB/USB_D+: J9.A6 (D+), J9.B6 (D+); also elsewhere on the board
/Microcontroller/USB/USB_D-: J9.A7 (D-), J9.B7 (D-); also elsewhere on the board
/Microcontroller/USB/USB_SENSE: R26.2; also elsewhere on the board
GND: C32.2, C33.2, J9.A1 (GND), J9.A12 (GND), J9.B1 (GND), J9.B12 (GND), J9.S1 (SHIELD), R27.2, R28.2; also elsewhere on the board
unnamed: J9.A5 (CC1), R27.1
unnamed: J9.B5 (CC2), R28.1
VBUS: C32.1, C33.1, J9.A4 (VBUS), J9.A9 (VBUS), J9.B4 (VBUS), J9.B9 (VBUS), R26.1; also elsewhere on the board

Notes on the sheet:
USB
USB Connection Circuit
500mA MAX
